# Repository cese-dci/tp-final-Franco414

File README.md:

## Trabajo práctico final de la asignatura DCI ##
Este repositorio contiene el trabajo práctico final para la asignatura de Diseño de Circuitos Impresos de la carrera de posgrado de FIUBA.

* Autor: Geronimo, Franco Ezequiel
* Título corto del trabajo:  Replica Modulo Driver 16-Ch PWM con PCA9685
* Descripción:  El presente trabajo consiste en elaborar un nuevo diseño para el módulo Adafruit controlador de 16 canales PWM/Servos mediante I2C con el integrado PCA9685.
  
## Imagenes de la PCB ##

## Licencia de este trabajo ##
Esta obra está bajo una Licencia Creative Commons Atribución 4.0 Internacional. 2021

## Estructura del TP FINAL ##

Se propone y se pide utilizar la siguiente estructura.

* doc: Toda la información sobre el circuito, principalmente de autoría o procesamiento propio. Por ejemplo:
  * Notas de ingeniería propias.
  * Notas de aplicación propias.
  * Estudios previos, estado del arte, resumen de las investigaciones.
  * Notas con cálculos.
  * Dibujos adicionales.
  * Fotos de los prototipos.
  * Presupuestos, cotizaciones.
* info: Toda la iformación recolectada, principalmente de terceros, como por ejemplo:
  * Hojas de datos.
  * Notas de aplicación.
  * Info de productos comerciales.
  * Info en internet.
* pcb: Archivos de diseño esquemático y pcb.

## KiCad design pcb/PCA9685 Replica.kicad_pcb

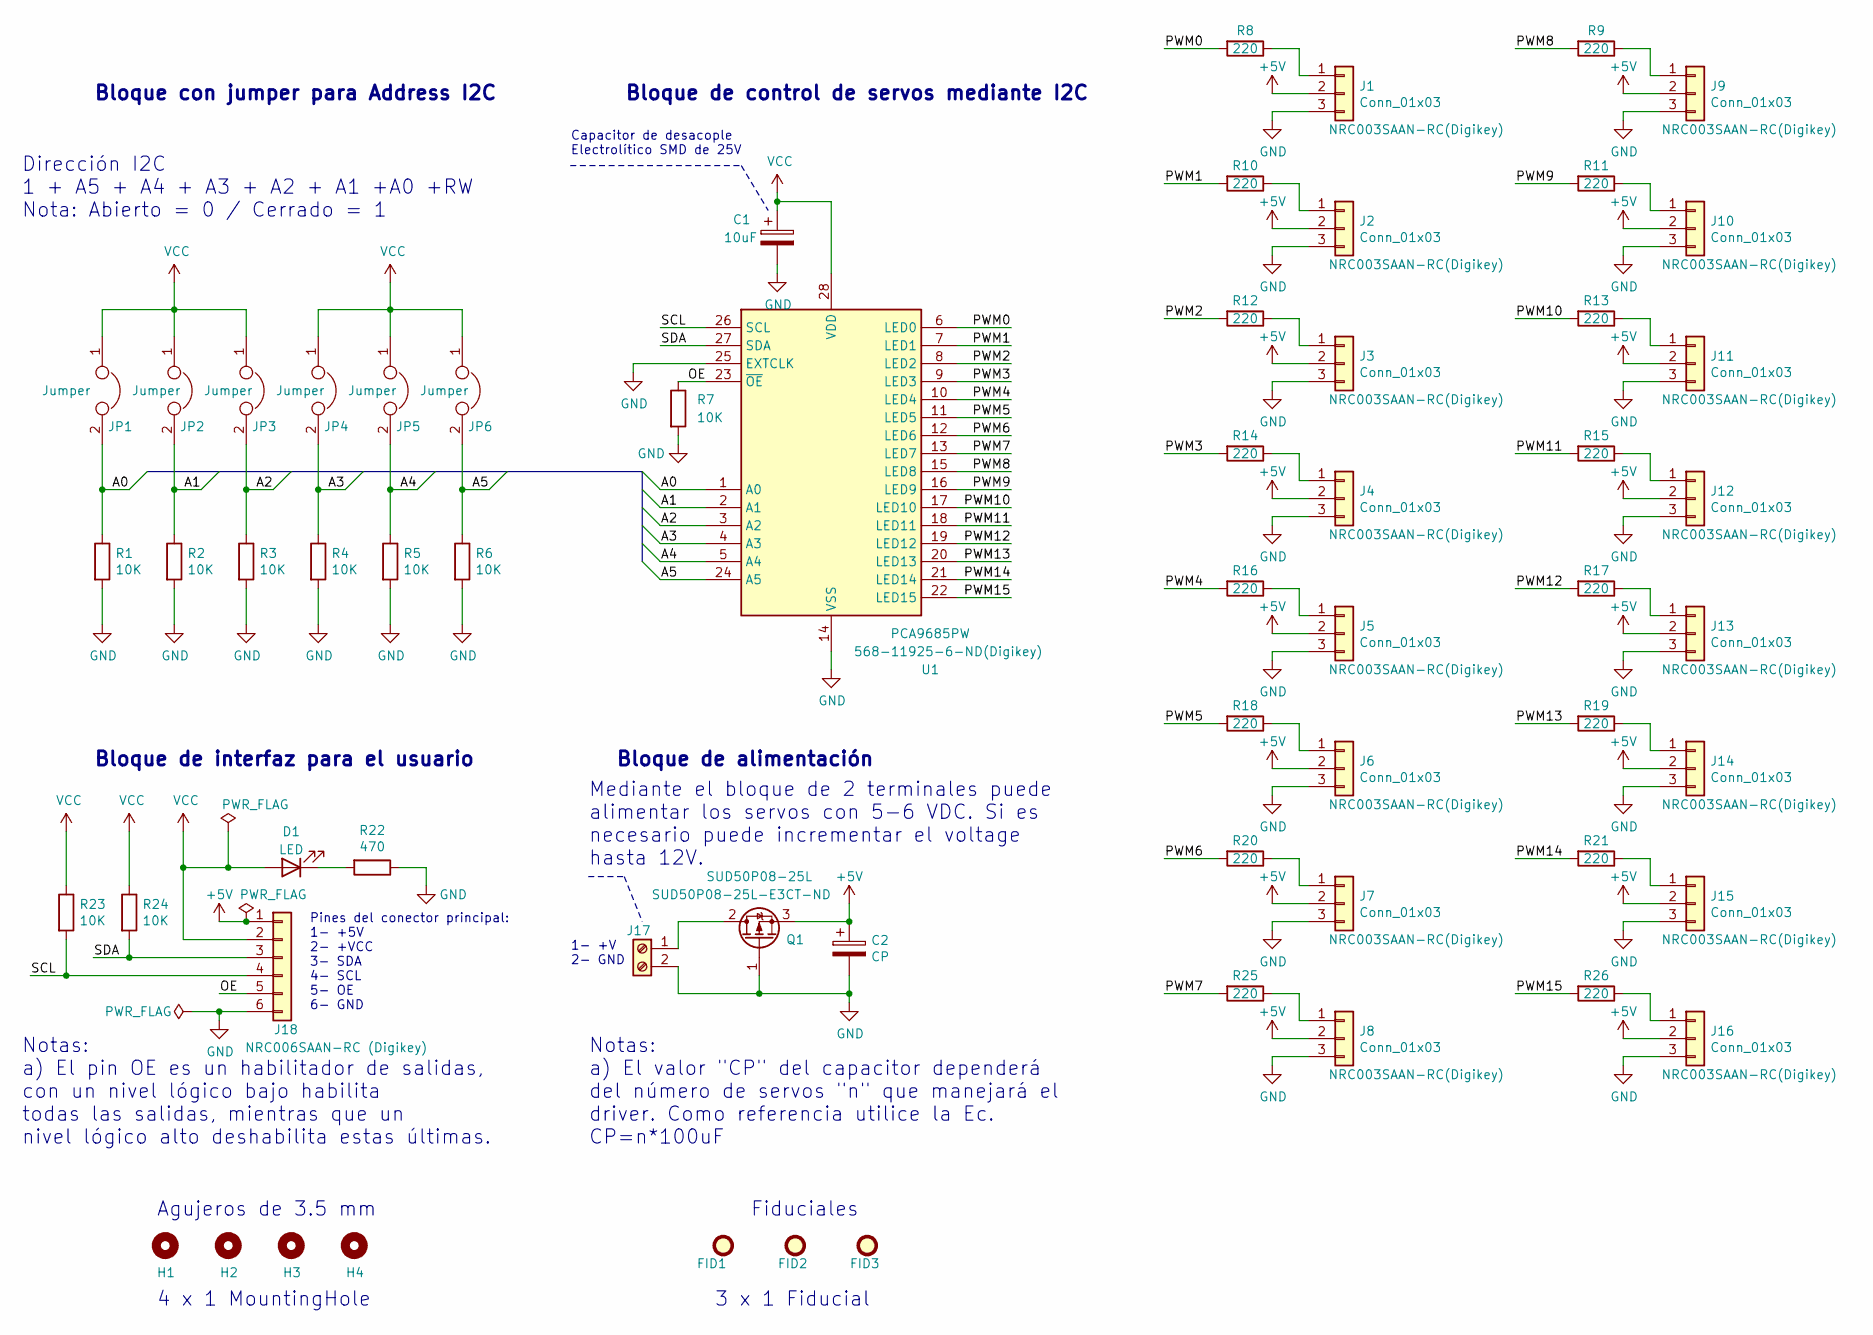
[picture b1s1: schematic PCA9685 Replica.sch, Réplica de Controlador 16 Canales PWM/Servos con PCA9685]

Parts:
C1: 10uF; CP_Elec_5x5.4
C2: CP; CP_Radial_D12.5mm_P5.00mm
D1: LED; LED_0805_2012Metric_Castellated
FID1, FID2, FID3: Fiducial; Fiducial_1mm_Mask2mm
H1, H2, H3, H4: MountingHole; MountingHole_3.5mm_Pad
J1, J2, J3, J4, J5, J6, J7, J8, J9, J10, J11, J12, J13, J14, J15, J16: Conn_01x03; PinHeader_1x03_P2.54mm_Vertical
J17: Screw_Terminal_01x02; TerminalBlock_Phoenix_MKDS-1,5-2_1x02_P5.00mm_Horizontal
J18: Conn_01x06; PinHeader_1x06_P2.54mm_Vertical
JP1, JP2, JP3, JP4, JP5, JP6: Jumper; SolderJumper-2_P1.3mm_Open_RoundedPad1.0x1.5mm
Q1: SUD50P08-25L; TO-252-2
R1, R2, R3, R4, R5, R6, R7, R23, R24: 10K; R_0805_2012Metric
R8, R9, R10, R11, R12, R13, R14, R15, R16, R17, R18, R19, R20, R21, R25, R26: 220; R_0805_2012Metric
R22: 470; R_0805_2012Metric
U1: PCA9685PW; TSSOP-28_4.4x9.7mm_P0.65mm

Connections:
+5V: C2.1, J1.2, J2.2, J3.2, J4.2, J5.2, J6.2, J7.2, J8.2, J9.2, J10.2, J11.2, J12.2, J13.2, J14.2, J15.2, J16.2, J18.1, Q1.3 (S)
/A0: JP1.2, R1.1, U1.1 (A0)
/A1: JP2.2, R2.1, U1.2 (A1)
/A2: JP3.2, R3.1, U1.3 (A2)
/A3: JP4.2, R4.1, U1.4 (A3)
/A4: JP5.2, R5.1, U1.5 (A4)
/A5: JP6.2, R6.1, U1.24 (A5)
/OE: J18.5, R7.1, U1.23 (~OE)
/PWM0: R8.2, U1.6 (LED0)
/PWM1: R10.2, U1.7 (LED1)
/PWM2: R12.2, U1.8 (LED2)
/PWM3: R14.2, U1.9 (LED3)
/PWM4: R16.2, U1.10 (LED4)
/PWM5: R18.2, U1.11 (LED5)
/PWM6: R20.2, U1.12 (LED6)
/PWM7: R25.2, U1.13 (LED7)
/PWM8: R9.2, U1.15 (LED8)
/PWM9: R11.2, U1.16 (LED9)
/PWM10: R13.2, U1.17 (LED10)
/PWM11: R15.2, U1.18 (LED11)
/PWM12: R17.2, U1.19 (LED12)
/PWM13: R19.2, U1.20 (LED13)
/PWM14: R21.2, U1.21 (LED14)
/PWM15: R26.2, U1.22 (LED15)
/SCL: J18.4, R23.2, U1.26 (SCL)
/SDA: J18.3, R24.2, U1.27 (SDA)
GND: C1.2, C2.2, J1.3, J2.3, J3.3, J4.3, J5.3, J6.3, J7.3, J8.3, J9.3, J10.3, J11.3, J12.3, J13.3, J14.3, J15.3, J16.3, J17.2, J18.6, Q1.1 (G), R1.2, R2.2, R3.2, R4.2, R5.2, R6.2, R7.2, R22.1, U1.14 (VSS), U1.25 (EXTCLK)
unnamed: D1.1 (K), R22.2
unnamed: J1.1, R8.1
unnamed: J2.1, R10.1
unnamed: J3.1, R12.1
unnamed: J4.1, R14.1
unnamed: J5.1, R16.1
unnamed: J6.1, R18.1
unnamed: J7.1, R20.1
unnamed: J8.1, R25.1
unnamed: J9.1, R9.1
unnamed: J10.1, R11.1
unnamed: J11.1, R13.1
unnamed: J12.1, R15.1
unnamed: J13.1, R17.1
unnamed: J14.1, R19.1
unnamed: J15.1, R21.1
unnamed: J16.1, R26.1
unnamed: J17.1, Q1.2 (D)
VCC: C1.1, D1.2 (A), J18.2, JP1.1, JP2.1, JP3.1, JP4.1, JP5.1, JP6.1, R23.1, R24.1, U1.28 (VDD)

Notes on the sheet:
Dirección I2C 1 + A5 + A4 + A3 + A2 + A1 +A0 +RW Nota: Abierto = 0 / Cerrado = 1
Capacitor de desacople Electrolítico SMD de 25V
Notas: a) El pin OE es un habilitador de salidas, con un nivel lógico bajo habilita todas las salidas, mientras que un nivel lógico alto deshabilita estas últimas.
Bloque de interfaz para el usuario
Bloque de alimentación
Bloque de control de servos mediante I2C
Bloque con jumper para Address I2C
Agujeros de 3.5 mm
Fiduciales
Notas: a) El valor "CP" del capacitor dependerá del número de servos "n" que manejará el driver. Como referencia utilice la Ec. CP=n*100uF
Pines del conector principal: 1- +5V 2- +VCC 3- SDA 4- SCL 5- OE 6- GND
4 x 1 MountingHole
3 x 1 Fiducial
Mediante el bloque de 2 terminales puede alimentar los servos con 5-6 VDC. Si es necesario puede incrementar el voltage hasta 12V.
1- +V 2- GND

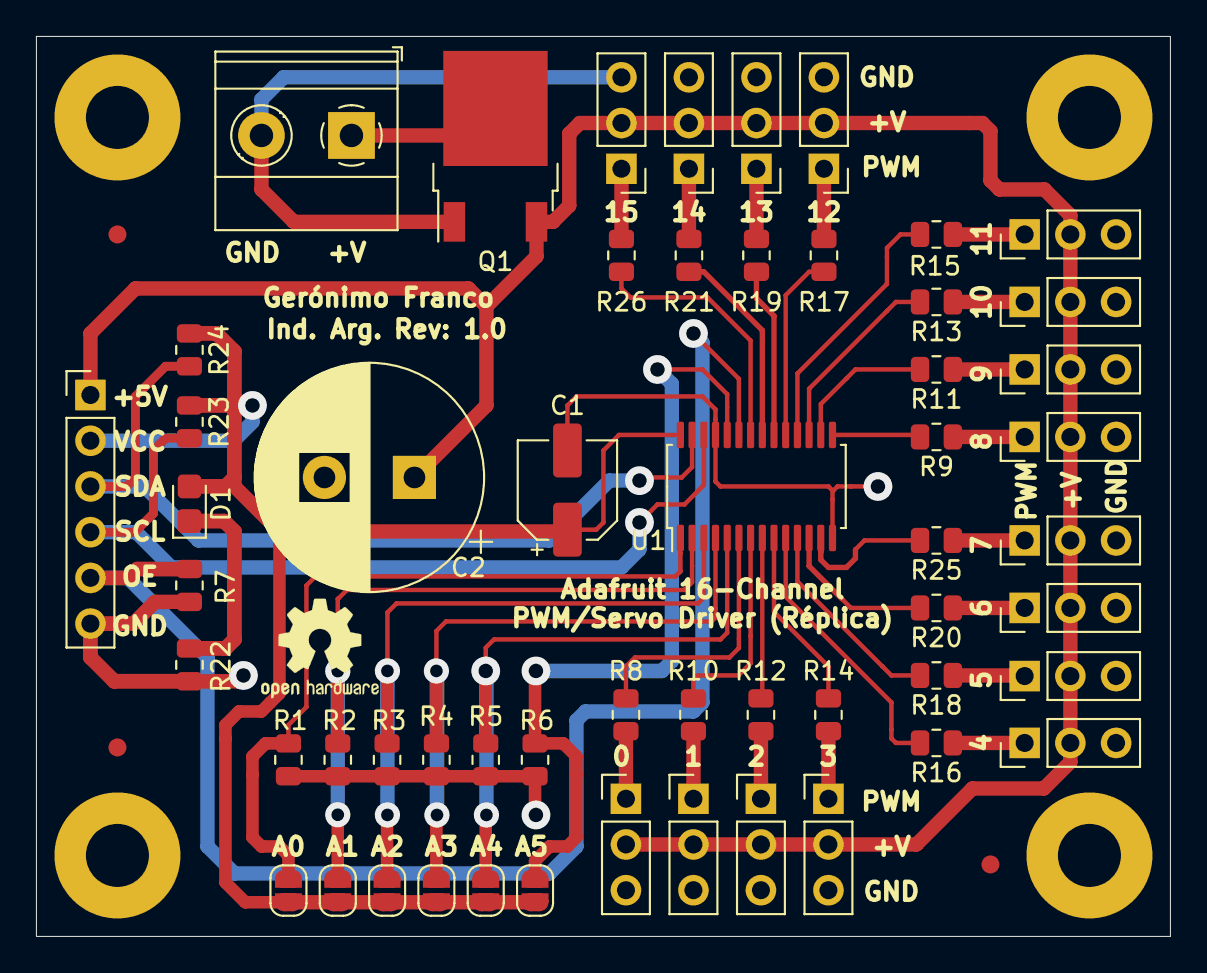
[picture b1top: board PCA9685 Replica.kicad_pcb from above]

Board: 2 copper layers, 63.0 x 50.0 mm, 62 parts (0 on the bottom side), 46 nets.

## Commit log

2021-09-09 Update: Repo Markdown
2021-09-09 Add Images and Schematic
2021-09-09 ADD: Datasheets
2021-09-09 Add pdf file with update sch
2021-09-21 Add PDF file of the module
2021-09-21 Update folder info
2021-09-21 unnecessary files deleted
2021-09-21 Update pcb folder
2021-10-14 update project
2021-10-14 update pcb
